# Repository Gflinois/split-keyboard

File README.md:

# Split-keyboard

This Git project contains everything that is needed for the construction of split 60 % keyboard. The layout used is a custom one (see layout) base on international qwerty. The project include:

- pcb files of a proof of concept with 4 switches
- pcb files of each of the keyboard sides
- a shopping list for all needed components
- cad, stl and gcode for the case files (gcode for an ender 3 with a probe)
- cad, stl and gcode for the keycaps (gcode for an anycubic proton)
- the driver module to use it on linux
- the driver module to use it on windows

## Layout

## Electronic specifiactions

This keyboard is a usb-c teather based one (no battey nor wireless connection provided yet). It is powered by an Atmega 328P stolen on an old arduino nano.

## Contribution

Contributions to this Git project are welcome! Please submit pull requests to the `dev` branch and include a detailed description of your changes.

## License

This project is licensed under the MIT License. See the `LICENSE` file for details.

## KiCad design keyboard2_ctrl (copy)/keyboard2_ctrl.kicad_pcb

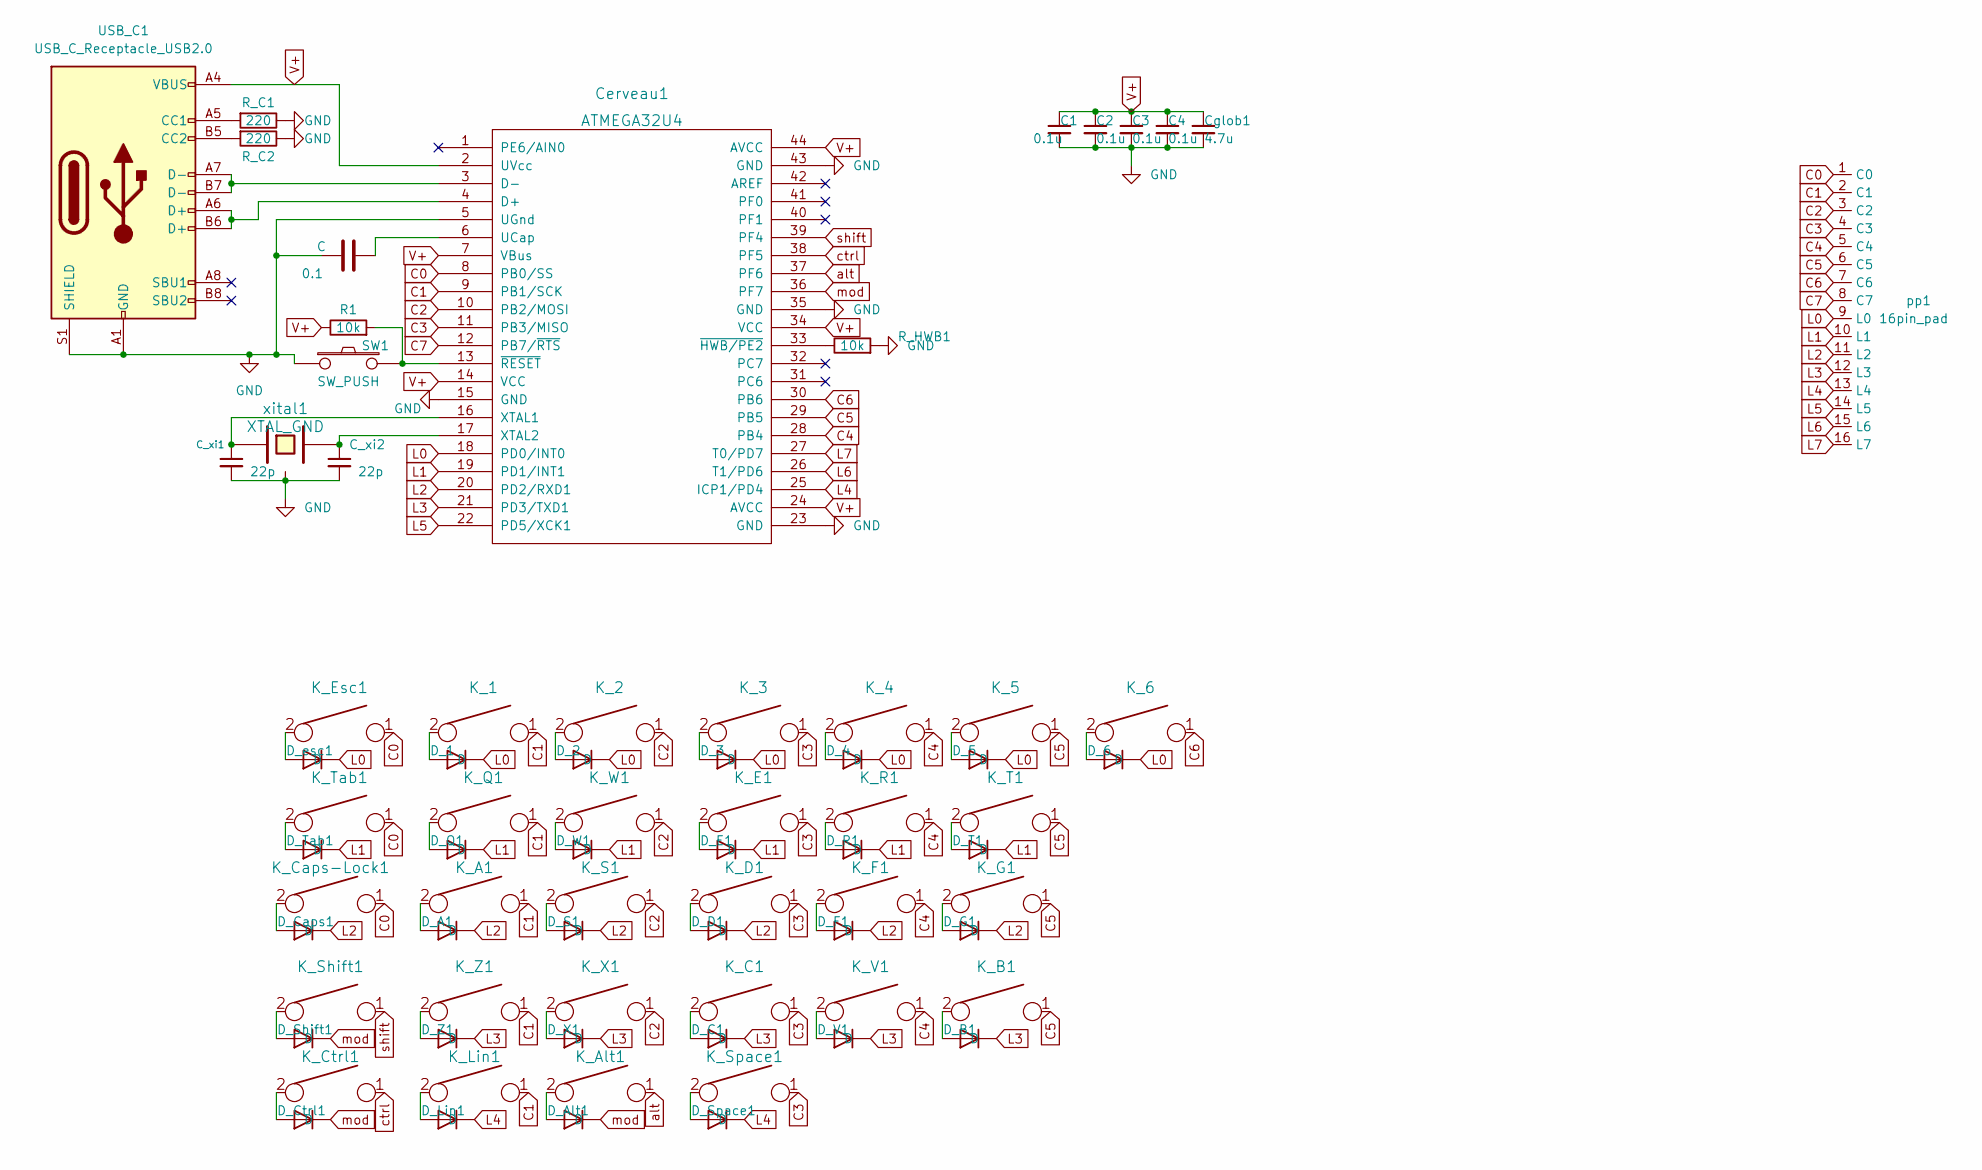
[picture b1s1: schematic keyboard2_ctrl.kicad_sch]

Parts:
0.1: C; C_0805_2012Metric
C1, C2, C3, C4: 0.1u; C_0805_2012Metric
C_xi1, C_xi2: 22p; C_0805_2012Metric
Cerveau1: ATMEGA32U4; TQFP-44_10x10mm_P0.8mm
Cglob1: 4.7u; C_0805_2012Metric
D_1, D_2, D_3, D_4, D_5, D_6: D; C_0805_2012Metric
D_A1: D; C_0805_2012Metric
D_Alt1: D; C_0805_2012Metric
D_B1: D; C_0805_2012Metric
D_C1: D; C_0805_2012Metric
D_Caps1: D; C_0805_2012Metric
D_Ctrl1: D; C_0805_2012Metric
D_D1: D; C_0805_2012Metric
D_E1: D; C_0805_2012Metric
D_F1: D; C_0805_2012Metric
D_G1: D; C_0805_2012Metric
D_Lin1: D; C_0805_2012Metric
D_Q1: D; C_0805_2012Metric
D_R1: D; C_0805_2012Metric
D_S1: D; C_0805_2012Metric
D_Shift1: D; C_0805_2012Metric
D_Space1: D; C_0805_2012Metric
D_T1: D; C_0805_2012Metric
D_Tab1: D; C_0805_2012Metric
D_V1: D; C_0805_2012Metric
D_W1: D; C_0805_2012Metric
D_X1: D; C_0805_2012Metric
D_Z1: D; C_0805_2012Metric
D_esc1: D; C_0805_2012Metric
K_1, K_2, K_3, K_4, K_5, K_6: KEYSW; SW_Cherry_MX_1.00u_PCB
K_A1: KEYSW; SW_Cherry_MX_1.00u_PCB
K_Alt1: KEYSW; SW_Cherry_MX_1.50u_PCB
K_B1: KEYSW; SW_Cherry_MX_1.00u_PCB
K_C1: KEYSW; SW_Cherry_MX_1.00u_PCB
K_Caps-Lock1: KEYSW; SW_Cherry_MX_1.75u_PCB
K_Ctrl1: KEYSW; SW_Cherry_MX_1.50u_PCB
K_D1: KEYSW; SW_Cherry_MX_1.00u_PCB
K_E1: KEYSW; SW_Cherry_MX_1.00u_PCB
K_Esc1: KEYSW; SW_Cherry_MX_1.00u_PCB
K_F1: KEYSW; SW_Cherry_MX_1.00u_PCB
K_G1: KEYSW; SW_Cherry_MX_1.00u_PCB
K_Lin1: KEYSW; SW_Cherry_MX_1.00u_PCB
K_Q1: KEYSW; SW_Cherry_MX_1.00u_PCB
K_R1: KEYSW; SW_Cherry_MX_1.00u_PCB
K_S1: KEYSW; SW_Cherry_MX_1.00u_PCB
K_Shift1: KEYSW; SW_Cherry_MX_2.25u_PCB
K_Space1: KEYSW; SW_Cherry_MX_2.75u_PCB
K_T1: KEYSW; SW_Cherry_MX_1.00u_PCB
K_Tab1: KEYSW; SW_Cherry_MX_1.50u_PCB
K_V1: KEYSW; SW_Cherry_MX_1.00u_PCB
K_W1: KEYSW; SW_Cherry_MX_1.00u_PCB
K_X1: KEYSW; SW_Cherry_MX_1.00u_PCB
K_Z1: KEYSW; SW_Cherry_MX_1.00u_PCB
R1: 10k; R_0805_2012Metric
R_C1, R_C2: 220; R_0805_2012Metric
R_HWB1: 10k; R_0805_2012Metric
SW1: SW_PUSH; SW_SPST_TL3342
USB_C1: USB_C_Receptacle_USB2.0; USB_C_Receptacle_GCT_USB4085
pp1: 16pin_pad
xital1: XTAL_GND; Crystal_SMD_SeikoEpson_TSX3225-4Pin_3.2x2.5mm_HandSoldering

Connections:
C0: Cerveau1.8 (PB0/SS), K_Caps-Lock1.1, K_Esc1.1, K_Tab1.1, pp1.1 (C0)
C1: Cerveau1.9 (PB1/SCK), K_1.1, K_A1.1, K_Lin1.1, K_Q1.1, K_Z1.1, pp1.2 (C1)
C2: Cerveau1.10 (PB2/MOSI), K_2.1, K_S1.1, K_W1.1, K_X1.1, pp1.3 (C2)
C3: Cerveau1.11 (PB3/MISO), K_3.1, K_C1.1, K_D1.1, K_E1.1, K_Space1.1, pp1.4 (C3)
C4: Cerveau1.28 (PB4), K_4.1, K_F1.1, K_R1.1, K_V1.1, pp1.5 (C4)
C5: Cerveau1.29 (PB5), K_5.1, K_B1.1, K_G1.1, K_T1.1, pp1.6 (C5)
C6: Cerveau1.30 (PB6), K_6.1, pp1.7 (C6)
C7: Cerveau1.12 (PB7/~RTS), pp1.8 (C7)
GND: 0.1.1, C1.2, C2.2, C3.2, C4.2, C_xi1.2, C_xi2.2, Cerveau1.5 (UGnd), Cerveau1.15 (GND), Cerveau1.23 (GND), Cerveau1.35 (GND), Cerveau1.43 (GND), Cglob1.2, R_C1.1, R_C2.1, R_HWB1.2, SW1.1, USB_C1.A1 (GND), USB_C1.A12 (GND), USB_C1.B1 (GND), USB_C1.B12 (GND), USB_C1.S1 (SHIELD), xital1.3
L0: Cerveau1.18 (PD0/INT0), D_1.1 (K), D_2.1 (K), D_3.1 (K), D_4.1 (K), D_5.1 (K), D_6.1 (K), D_esc1.1 (K), pp1.9 (L0)
L1: Cerveau1.19 (PD1/INT1), D_E1.1 (K), D_Q1.1 (K), D_R1.1 (K), D_T1.1 (K), D_Tab1.1 (K), D_W1.1 (K), pp1.10 (L1)
L2: Cerveau1.20 (PD2/RXD1), D_A1.1 (K), D_Caps1.1 (K), D_D1.1 (K), D_F1.1 (K), D_G1.1 (K), D_S1.1 (K), pp1.11 (L2)
L3: Cerveau1.21 (PD3/TXD1), D_B1.1 (K), D_C1.1 (K), D_V1.1 (K), D_X1.1 (K), D_Z1.1 (K), pp1.12 (L3)
L4: Cerveau1.25 (ICP1/PD4), D_Lin1.1 (K), D_Space1.1 (K), pp1.13 (L4)
L5: Cerveau1.22 (PD5/XCK1), pp1.14 (L5)
L6: Cerveau1.26 (T1/PD6), pp1.15 (L6)
L7: Cerveau1.27 (T0/PD7), pp1.16 (L7)
unnamed: 0.1.2, Cerveau1.6 (UCap)
unnamed: C_xi1.1, Cerveau1.16 (XTAL1), xital1.1
unnamed: C_xi2.1, Cerveau1.17 (XTAL2), xital1.2
unnamed: Cerveau1.3 (D-), USB_C1.A7 (D-), USB_C1.B7 (D-)
unnamed: Cerveau1.4 (D+), USB_C1.A6 (D+), USB_C1.B6 (D+)
unnamed: Cerveau1.13 (~RESET), R1.2, SW1.2
unnamed: Cerveau1.33 (~HWB/PE2), R_HWB1.1
unnamed: D_1.2 (A), K_1.2
unnamed: D_2.2 (A), K_2.2
unnamed: D_3.2 (A), K_3.2
unnamed: D_4.2 (A), K_4.2
unnamed: D_5.2 (A), K_5.2
unnamed: D_6.2 (A), K_6.2
unnamed: D_A1.2 (A), K_A1.2
unnamed: D_Alt1.2 (A), K_Alt1.2
unnamed: D_B1.2 (A), K_B1.2
unnamed: D_C1.2 (A), K_C1.2
unnamed: D_Caps1.2 (A), K_Caps-Lock1.2
unnamed: D_Ctrl1.2 (A), K_Ctrl1.2
unnamed: D_D1.2 (A), K_D1.2
unnamed: D_E1.2 (A), K_E1.2
unnamed: D_F1.2 (A), K_F1.2
unnamed: D_G1.2 (A), K_G1.2
unnamed: D_Lin1.2 (A), K_Lin1.2
unnamed: D_Q1.2 (A), K_Q1.2
unnamed: D_R1.2 (A), K_R1.2
unnamed: D_S1.2 (A), K_S1.2
unnamed: D_Shift1.2 (A), K_Shift1.2
unnamed: D_Space1.2 (A), K_Space1.2
unnamed: D_T1.2 (A), K_T1.2
unnamed: D_Tab1.2 (A), K_Tab1.2
unnamed: D_V1.2 (A), K_V1.2
unnamed: D_W1.2 (A), K_W1.2
unnamed: D_X1.2 (A), K_X1.2
unnamed: D_Z1.2 (A), K_Z1.2
unnamed: D_esc1.2 (A), K_Esc1.2
unnamed: R_C1.2, USB_C1.A5 (CC1)
unnamed: R_C2.2, USB_C1.B5 (CC2)
V+: C1.1, C2.1, C3.1, C4.1, Cerveau1.2 (UVcc), Cerveau1.7 (VBus), Cerveau1.14 (VCC), Cerveau1.24 (AVCC), Cerveau1.34 (VCC), Cerveau1.44 (AVCC), Cglob1.1, R1.1, USB_C1.A4 (VBUS), USB_C1.A9 (VBUS), USB_C1.B4 (VBUS), USB_C1.B9 (VBUS)
alt: Cerveau1.37 (PF6), K_Alt1.1
ctrl: Cerveau1.38 (PF5), K_Ctrl1.1
mod: Cerveau1.36 (PF7), D_Alt1.1 (K), D_Ctrl1.1 (K), D_Shift1.1 (K)
shift: Cerveau1.39 (PF4), K_Shift1.1

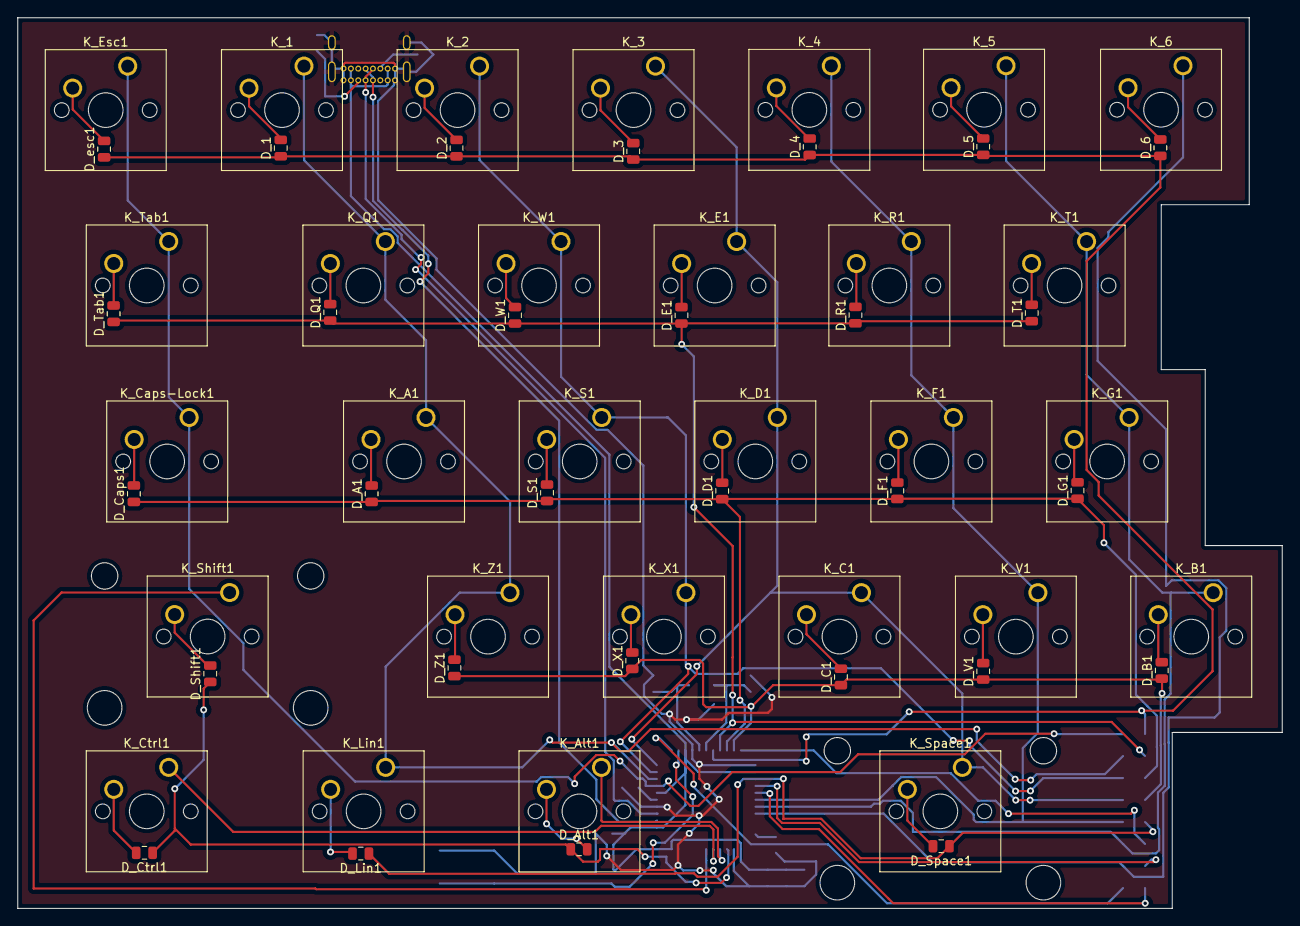
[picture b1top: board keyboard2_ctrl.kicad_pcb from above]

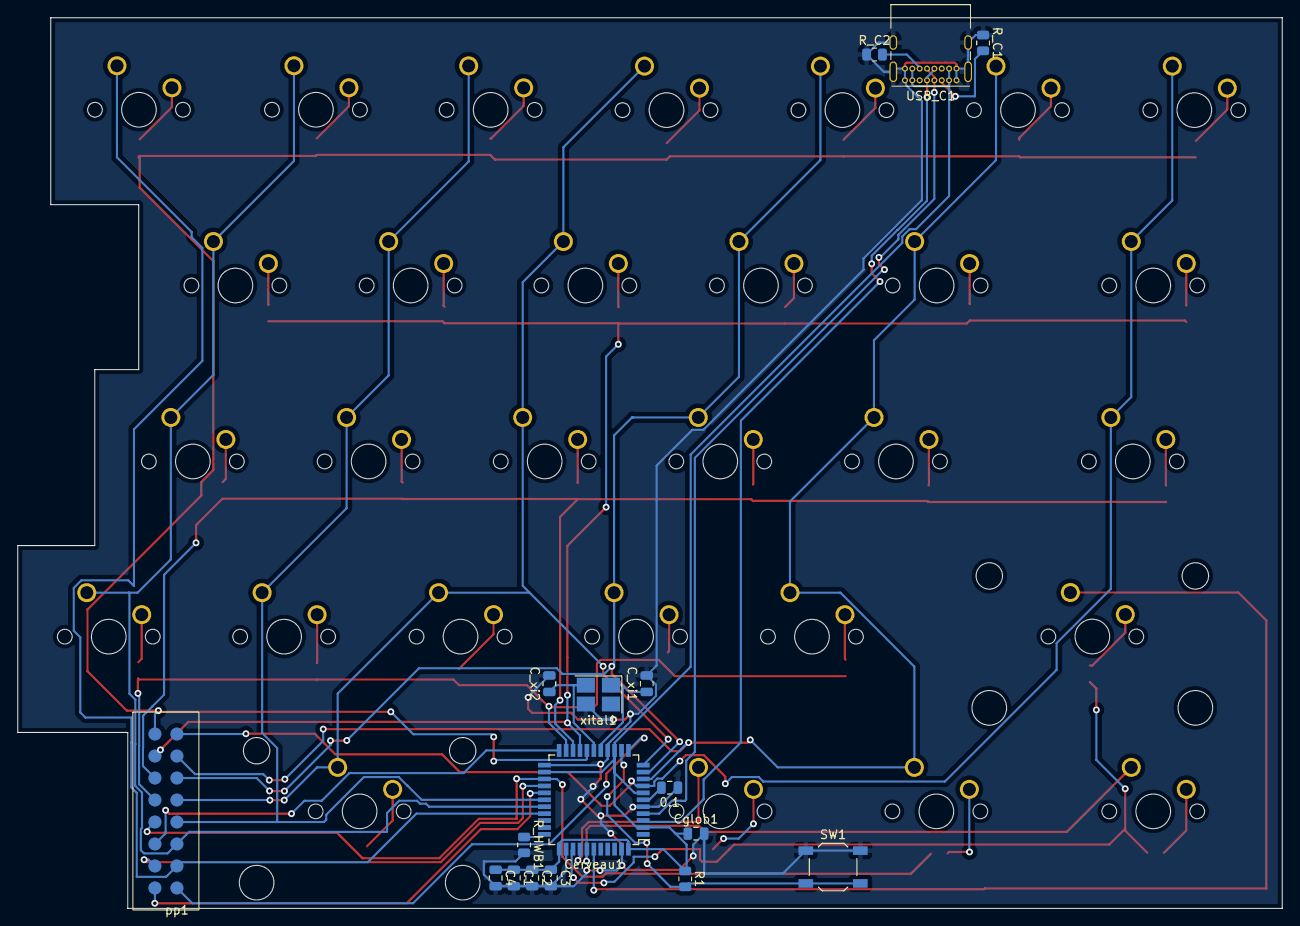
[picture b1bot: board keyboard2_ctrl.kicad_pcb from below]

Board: 2 copper layers, 146.1 x 102.9 mm, 75 parts (17 on the bottom side), 60 nets.

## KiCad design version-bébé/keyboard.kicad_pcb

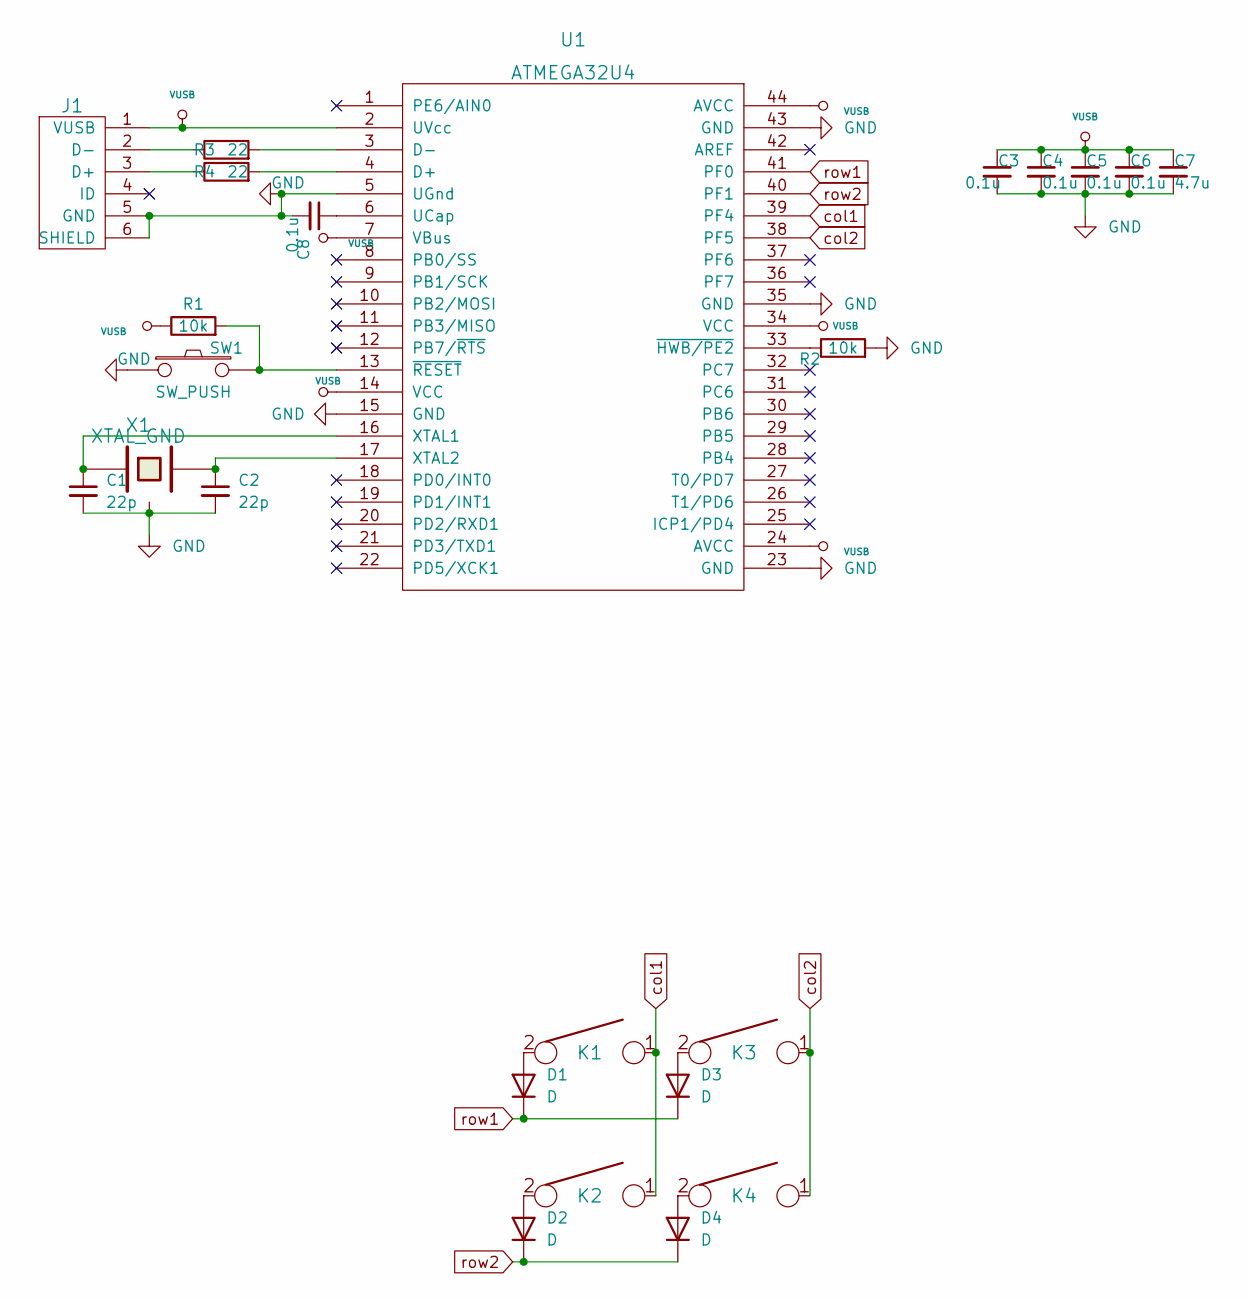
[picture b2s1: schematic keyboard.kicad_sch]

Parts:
C1, C2: 22p; C_0805_2012Metric
C3, C4, C5, C6, C8: 0.1u; C_0805_2012Metric
C7: 4.7u; C_0805_2012Metric
D1, D2, D3, D4: D; D_SOD123_axial
J1: USB_mini_micro_B; USB_miniB_hirose_5S8
K1, K2, K3, K4: KEYSW; SW_Matias_1.00u
R1, R2: 10k; R_0805_2012Metric
R3, R4: 22; R_0805_2012Metric
SW1: SW_PUSH; SW_SPST_TL3342
U1: ATMEGA32U4; TQFP-44_10x10mm_P0.8mm
X1: XTAL_GND; Crystal_SMD_SeikoEpson_TSX3225-4Pin_3.2x2.5mm_HandSoldering

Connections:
GND: C1.2, C2.2, C3.2, C4.2, C5.2, C6.2, C7.2, C8.2, J1.5 (GND), J1.6 (SHIELD), R2.2, SW1.1, U1.5 (UGnd), U1.15 (GND), U1.23 (GND), U1.35 (GND), U1.43 (GND), X1.3
unnamed: C1.1, U1.16 (XTAL1), X1.1
unnamed: C2.1, U1.17 (XTAL2), X1.2
unnamed: C8.1, U1.6 (UCap)
unnamed: D1.2 (A), K1.2
unnamed: D2.2 (A), K2.2
unnamed: D3.2 (A), K3.2
unnamed: D4.2 (A), K4.2
unnamed: J1.2 (D-), R3.1
unnamed: J1.3 (D+), R4.1
unnamed: R1.2, SW1.2, U1.13 (~RESET)
unnamed: R2.1, U1.33 (~HWB/PE2)
unnamed: R3.2, U1.3 (D-)
unnamed: R4.2, U1.4 (D+)
VUSB: C3.1, C4.1, C5.1, C6.1, C7.1, J1.1 (VUSB), R1.1, U1.2 (UVcc), U1.14 (VCC), U1.24 (AVCC), U1.34 (VCC), U1.44 (AVCC)
col1: K1.1, K2.1, U1.39 (PF4)
col2: K3.1, K4.1, U1.38 (PF5)
row1: D1.1 (K), D3.1 (K), U1.41 (PF0)
row2: D2.1 (K), D4.1 (K), U1.40 (PF1)

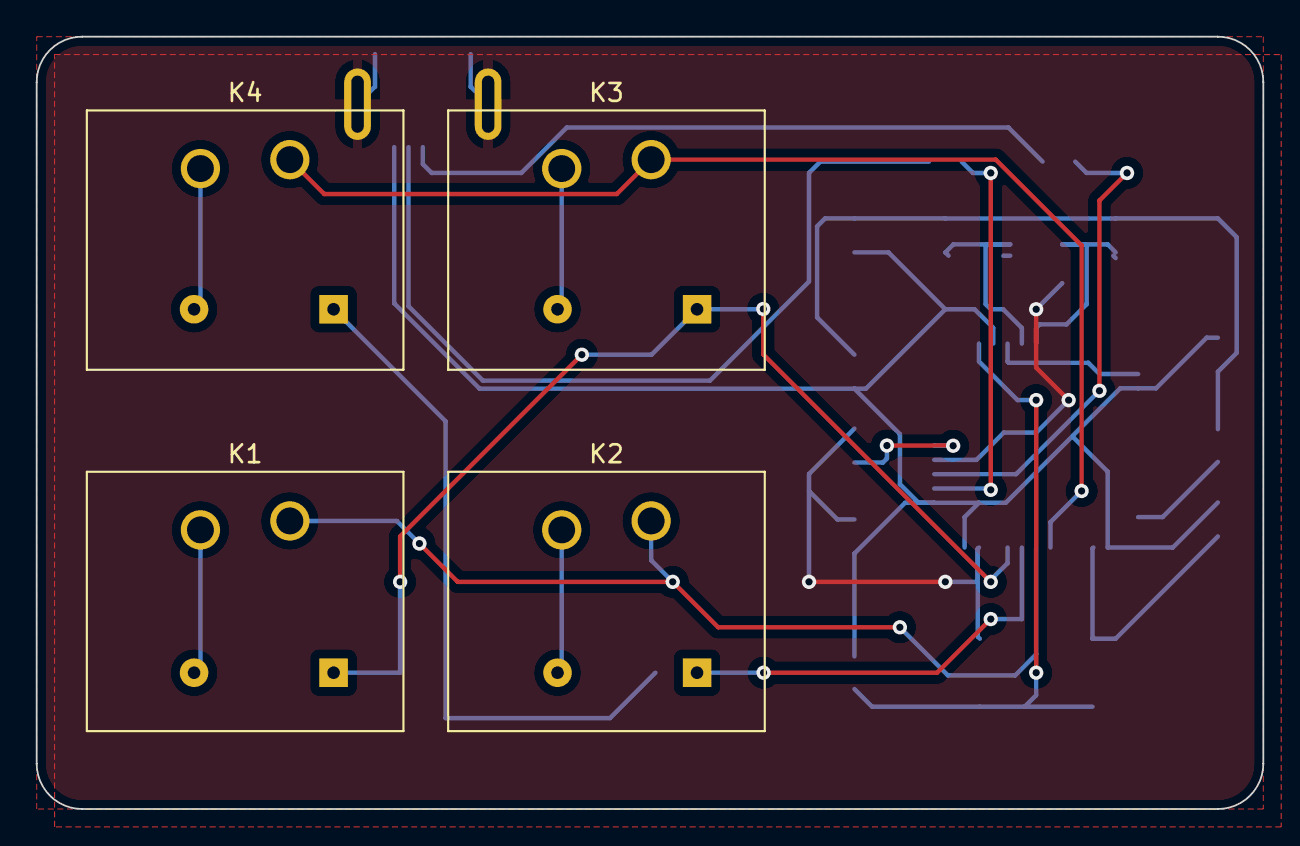
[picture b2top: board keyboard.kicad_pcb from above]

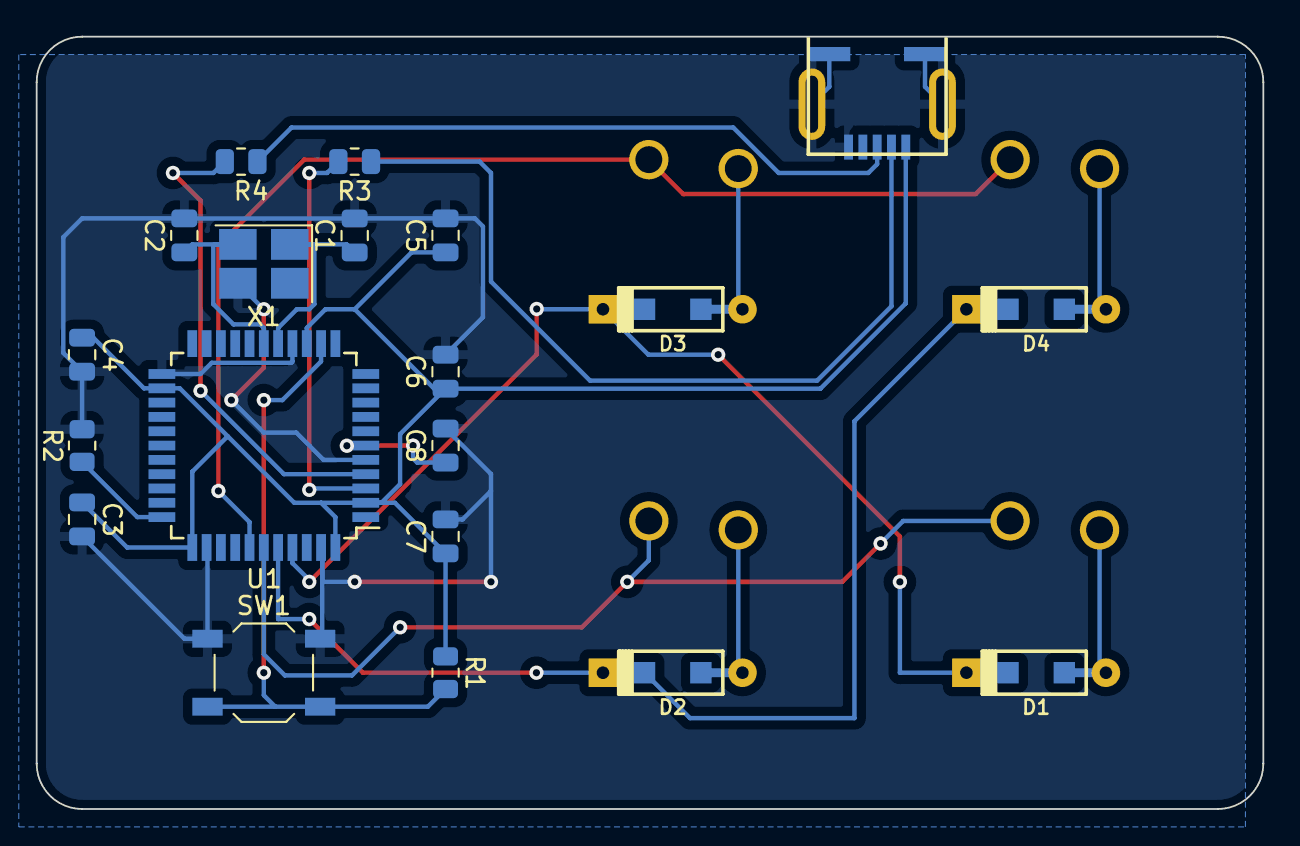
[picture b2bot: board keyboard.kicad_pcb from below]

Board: 2 copper layers, 68.6 x 43.2 mm, 24 parts (20 on the bottom side), 19 nets.

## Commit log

2023-04-14 bonjour git
2023-04-14 askip il faut dire ce que c'est un projet ducoup voilà
2023-04-18 jsplus en vrai lol
2023-04-19 ajout de mon keycap perso, test d'impression dans la journée pour le résultat
2023-04-21 nouvelles tailles de keycaps perso
2023-04-27 v2 des touches
2023-05-09 the right keycaps, begining work on the ergo case
2023-05-09 v2 plate & début lower case
2023-05-10 update assemblage et lower case
